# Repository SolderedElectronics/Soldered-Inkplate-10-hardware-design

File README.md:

## --- Product name --- Hardware design

|  |
| :----------------------------------------------------------: |
|      [--- product name ----](https://www.solde.red/SKU)      |

------ product description ------

## Repository contents

All Soldered hardware is designed in KiCAD, and repositories are organized in the following way:

- CAD folder - contains KiCAD files (Schematics, Board, Panel Board), organized by version. Change log lists all changes between versions.
- OUTPUTS - contains useful files, such as Bill of Materials (BOM), PDF of schematics, 3D .step file of the board and gerber files, organized by version. 

## Want to contribute?

All contributions are welcome, feel free to submit the pull request. If you discover a bug, please submit an issue or pull request. 

## About Soldered

At Soldered, we design and manufacture a wide selection of electronic products to help you turn your ideas into acts and bring you one step closer to your final project. Our products are intented for makers and crafted in-house by our experienced team in Osijek, Croatia. We believe that sharing is a crucial element for improvement and innovation, and we work hard to stay connected with all our makers regardless of their skill or experience level. Therefore, all our products are open-source. Finally, we always have your back. If you face any problem concerning either your shopping experience or your electronics project, our team will help you deal with it, offering efficient customer service and cost-free technical support anytime. Some of those might be useful for you:

- [Web Store](https://www.soldered.com)
- [Tutorials & Projects](https://soldered.com/blog)
- [Community & Technical support](https://community.soldered.com)
- [Custom PCBs](https://pcb.soldered.com)

## License info

All Soldered open-source hardware (OSH) is under The TAPR Open Hardware License. Read more in the LICENSE file. 

No warranty - all designs in this repository are distributed in the hope that they will be useful, but without any warranty. They are provided "AS IS", therefore without warranty of any kind, either expressed or implied. The entire quality and performance of what you do with the contents of this repository are your responsibility. In no event, Soldered (TAVU) will be liable for your damages, losses, including any general, special, incidental or consequential damage arising out of the use or inability to use the contents of this repository. 

Thank you from your fellow makers at Soldered.

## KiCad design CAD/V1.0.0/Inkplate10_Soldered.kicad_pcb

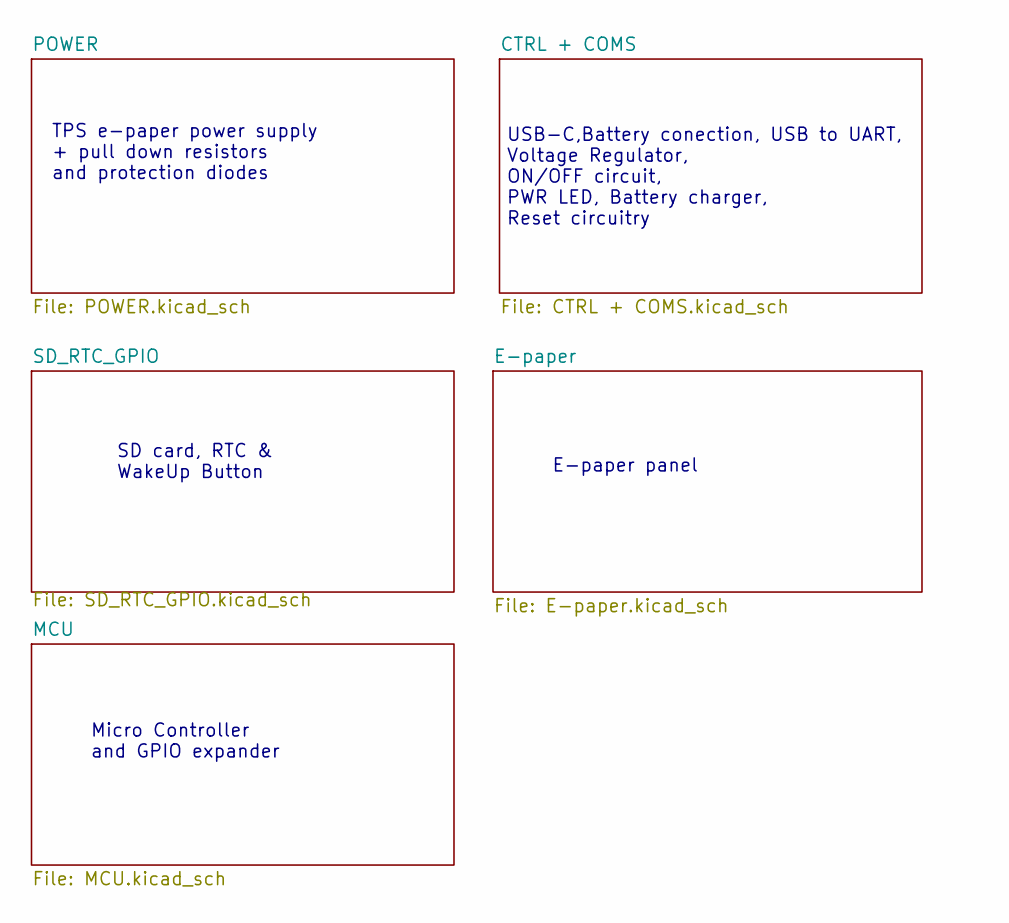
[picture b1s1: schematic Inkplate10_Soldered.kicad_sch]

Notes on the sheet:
SD card, RTC & WakeUp Button
TPS e-paper power supply + pull down resistors and protection diodes
E-paper panel
USB-C,Battery conection, USB to UART, Voltage Regulator, ON/OFF circuit, PWR LED, Battery charger, Reset circuitry
Micro Controller and GPIO expander

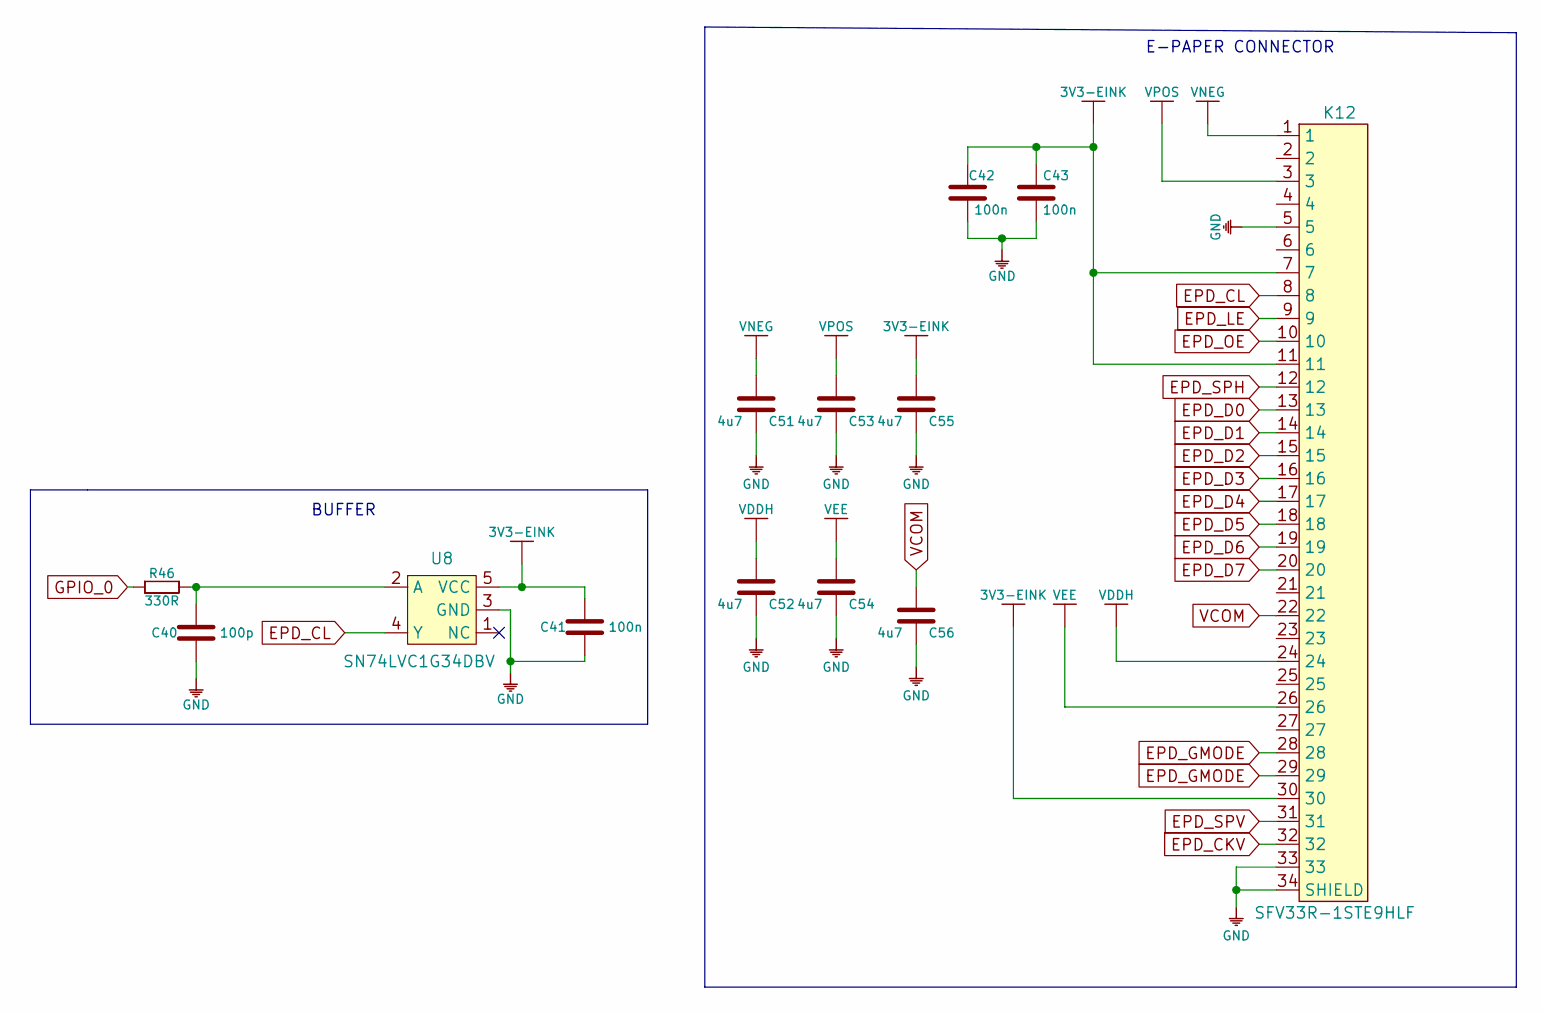
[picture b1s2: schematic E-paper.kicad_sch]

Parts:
C40: 100p; 0603C
C41, C42, C43: 100n; 0603C
C51, C52, C53, C54, C55, C56: 4u7; 0603C
K12: SFV33R-1STE9HLF
R46: 330R; 0603R
U8: SN74LVC1G34DBV

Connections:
3V3-EINK: C41.2, C42.2, C43.2, C55.2, K12.7, K12.11, K12.30, U8.5 (VCC); also elsewhere on the board
EPD_CKV: K12.32; also elsewhere on the board
EPD_CL: K12.8, U8.4 (Y)
EPD_D0: K12.13; also elsewhere on the board
EPD_D1: K12.14; also elsewhere on the board
EPD_D2: K12.15; also elsewhere on the board
EPD_D3: K12.16; also elsewhere on the board
EPD_D4: K12.17; also elsewhere on the board
EPD_D5: K12.18; also elsewhere on the board
EPD_D6: K12.19; also elsewhere on the board
EPD_D7: K12.20; also elsewhere on the board
EPD_GMODE: K12.28, K12.29; also elsewhere on the board
EPD_LE: K12.9; also elsewhere on the board
EPD_OE: K12.10; also elsewhere on the board
EPD_SPH: K12.12; also elsewhere on the board
EPD_SPV: K12.31; also elsewhere on the board
GND: C40.1, C41.1, C42.1, C43.1, C51.1, C52.1, C53.1, C54.1, C55.1, C56.1, K12.5, K12.33, K12.34 (SHIELD), U8.3 (GND); also elsewhere on the board
GPIO_0: R46.1; also elsewhere on the board
unnamed: C40.2, R46.2, U8.2 (A)
VCOM: C56.2, K12.22; also elsewhere on the board
VDDH: C52.2, K12.24; also elsewhere on the board
VEE: C54.2, K12.26; also elsewhere on the board
VNEG: C51.2, K12.1; also elsewhere on the board
VPOS: C53.2, K12.3; also elsewhere on the board

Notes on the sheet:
E-PAPER CONNECTOR
BUFFER

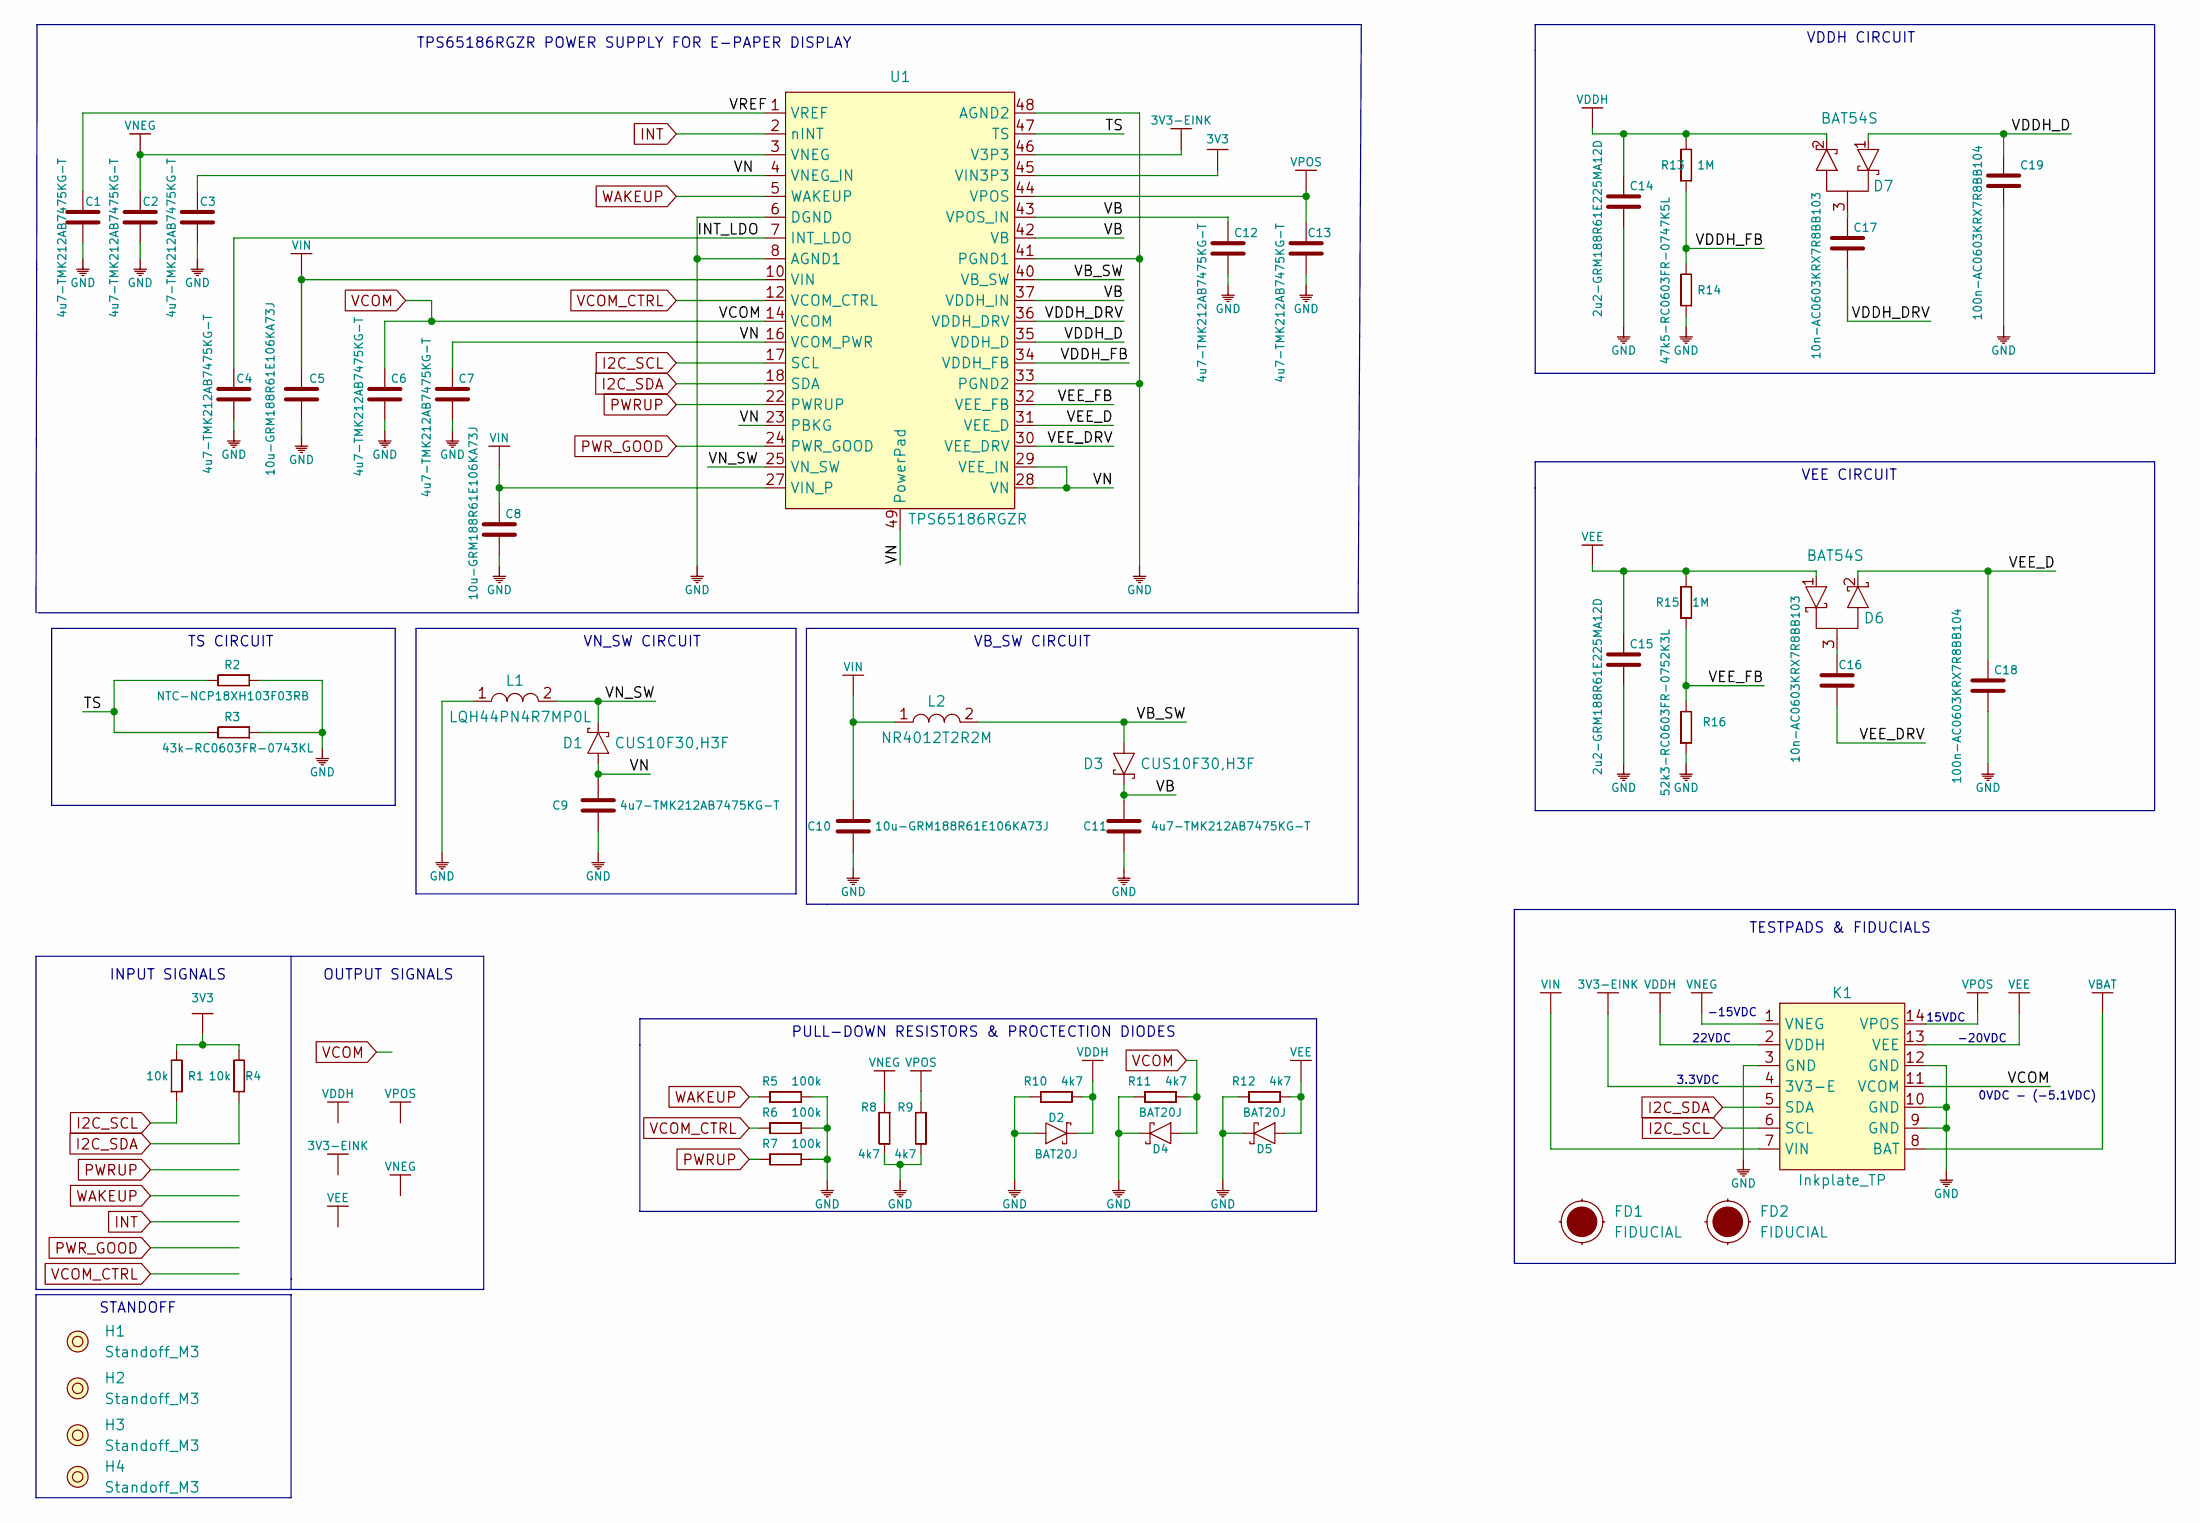
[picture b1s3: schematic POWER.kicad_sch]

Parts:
C1, C2, C3, C4, C6, C7, C9, C11, C12, C13: 4u7-TMK212AB7475KG-T; 0603C
C5, C8, C10: 10u-GRM188R61E106KA73J; 0603C
C14, C15: 2u2-GRM188R61E225MA12D; 0603C
C16, C17: 10n-AC0603KRX7R8BB103; 0603C
C18, C19: 100n-AC0603KRX7R8BB104; 0603C
D1, D3: CUS10F30,H3F; SOD-323-2
D2, D4, D5: BAT20J; SOD-323
D6, D7: BAT54S; SOT-23-3
FD1, FD2: FIDUCIAL; FIDUCIAL_23
H1, H2, H3, H4: Standoff_M3
K1: Inkplate_TP; INKPLATE TEST HEADER
L1: LQH44PN4R7MP0L; 1515L
L2: NR4012T2R2M; NR4012
R1, R4: 10k; 0603R
R2: NTC-NCP18XH103F03RB; 0603R
R3: 43k-RC0603FR-0743KL; 0603R
R5, R6, R7: 100k; 0603R
R8, R9, R10, R11, R12: 4k7; 0603R
R13, R15: 1M; 0603R
R14: 47k5-RC0603FR-0747K5L; 0603R
R16: 52k3-RC0603FR-0752K3L; 0603R
U1: TPS65186RGZR; VQFN-49

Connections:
3V3: R1.2, R4.2, U1.45 (VIN3P3); also elsewhere on the board
3V3-EINK: K1.4 (3V3-E), U1.46 (V3P3); also elsewhere on the board
/POWER/INT_LDO: C4.2, U1.7 (INT_LDO)
/POWER/TS: R2.2, R3.2, U1.47 (TS)
/POWER/VB: C11.2, C12.1, D3.1 (C), U1.37 (VDDH_IN), U1.42 (VB), U1.43 (VPOS_IN)
/POWER/VB_SW: D3.2 (A), L2.2, U1.40 (VB_SW)
/POWER/VDDH_D: C19.2, D7.1 (A), U1.35 (VDDH_D)
/POWER/VDDH_DRV: C17.1, U1.36 (VDDH_DRV)
/POWER/VDDH_FB: R13.1, R14.2, U1.34 (VDDH_FB)
/POWER/VEE_D: C18.2, D6.2 (K), U1.31 (VEE_D)
/POWER/VEE_DRV: C16.2, U1.30 (VEE_DRV)
/POWER/VEE_FB: R15.1, R16.2, U1.32 (VEE_FB)
/POWER/VN: C3.2, C7.1, C9.2, D1.2 (A), U1.4 (VNEG_IN), U1.16 (VCOM_PWR), U1.23 (PBKG), U1.28 (VN), U1.29 (VEE_IN), U1.49 (PowerPad)
/POWER/VN_SW: D1.1 (C), L1.2, U1.25 (VN_SW)
/POWER/VREF: C1.2, U1.1 (VREF)
GND: C1.1, C2.1, C3.1, C4.1, C5.1, C6.2, C7.2, C8.1, C9.1, C10.1, C11.1, C12.2, C13.2, C14.1, C15.1, C18.1, C19.1, D2.1 (A), D4.2 (C), D5.2 (C), K1.3 (GND), K1.9 (GND), K1.10 (GND), K1.12 (GND), L1.1, R2.1, R3.1, R5.2, R6.2, R7.2, R8.2, R9.2, R10.1, R11.1, R12.1, R14.1, R16.1, U1.6 (DGND), U1.8 (AGND1), U1.33 (PGND2), U1.41 (PGND1), U1.48 (AGND2); also elsewhere on the board
I2C_SCL: K1.6 (SCL), R1.1, U1.17 (SCL); also elsewhere on the board
I2C_SDA: K1.5 (SDA), R4.1, U1.18 (SDA); also elsewhere on the board
INT: U1.2 (nINT); also elsewhere on the board
unnamed: C16.1, D6.3
unnamed: C17.2, D7.3
PWRUP: R7.1, U1.22 (PWRUP); also elsewhere on the board
PWR_GOOD: U1.24 (PWR_GOOD); also elsewhere on the board
VBAT: K1.8 (BAT); also elsewhere on the board
VCOM: C6.1, D4.1 (A), K1.11 (VCOM), R11.2, U1.14 (VCOM); also elsewhere on the board
VCOM_CTRL: R6.1, U1.12 (VCOM_CTRL); also elsewhere on the board
VDDH: C14.2, D2.2 (C), D7.2 (K), K1.2 (VDDH), R10.2, R13.2; also elsewhere on the board
VEE: C15.2, D5.1 (A), D6.1 (A), K1.13 (VEE), R12.2, R15.2; also elsewhere on the board
VIN: C5.2, C8.2, C10.2, K1.7 (VIN), L2.1, U1.10 (VIN), U1.27 (VIN_P); also elsewhere on the board
VNEG: C2.2, K1.1 (VNEG), R8.1, U1.3 (VNEG); also elsewhere on the board
VPOS: C13.1, K1.14 (VPOS), R9.1, U1.44 (VPOS); also elsewhere on the board
WAKEUP: R5.1, U1.5 (WAKEUP); also elsewhere on the board

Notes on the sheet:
TPS65186RGZR POWER SUPPLY FOR E-PAPER DISPLAY
VB_SW CIRCUIT
VDDH CIRCUIT
VEE CIRCUIT
INPUT SIGNALS
OUTPUT SIGNALS
TS CIRCUIT
PULL-DOWN RESISTORS & PROCTECTION DIODES
TESTPADS & FIDUCIALS
VN_SW CIRCUIT
3.3VDC
-20VDC
22VDC
STANDOFF
0VDC - (-5.1VDC)
-15VDC
15VDC

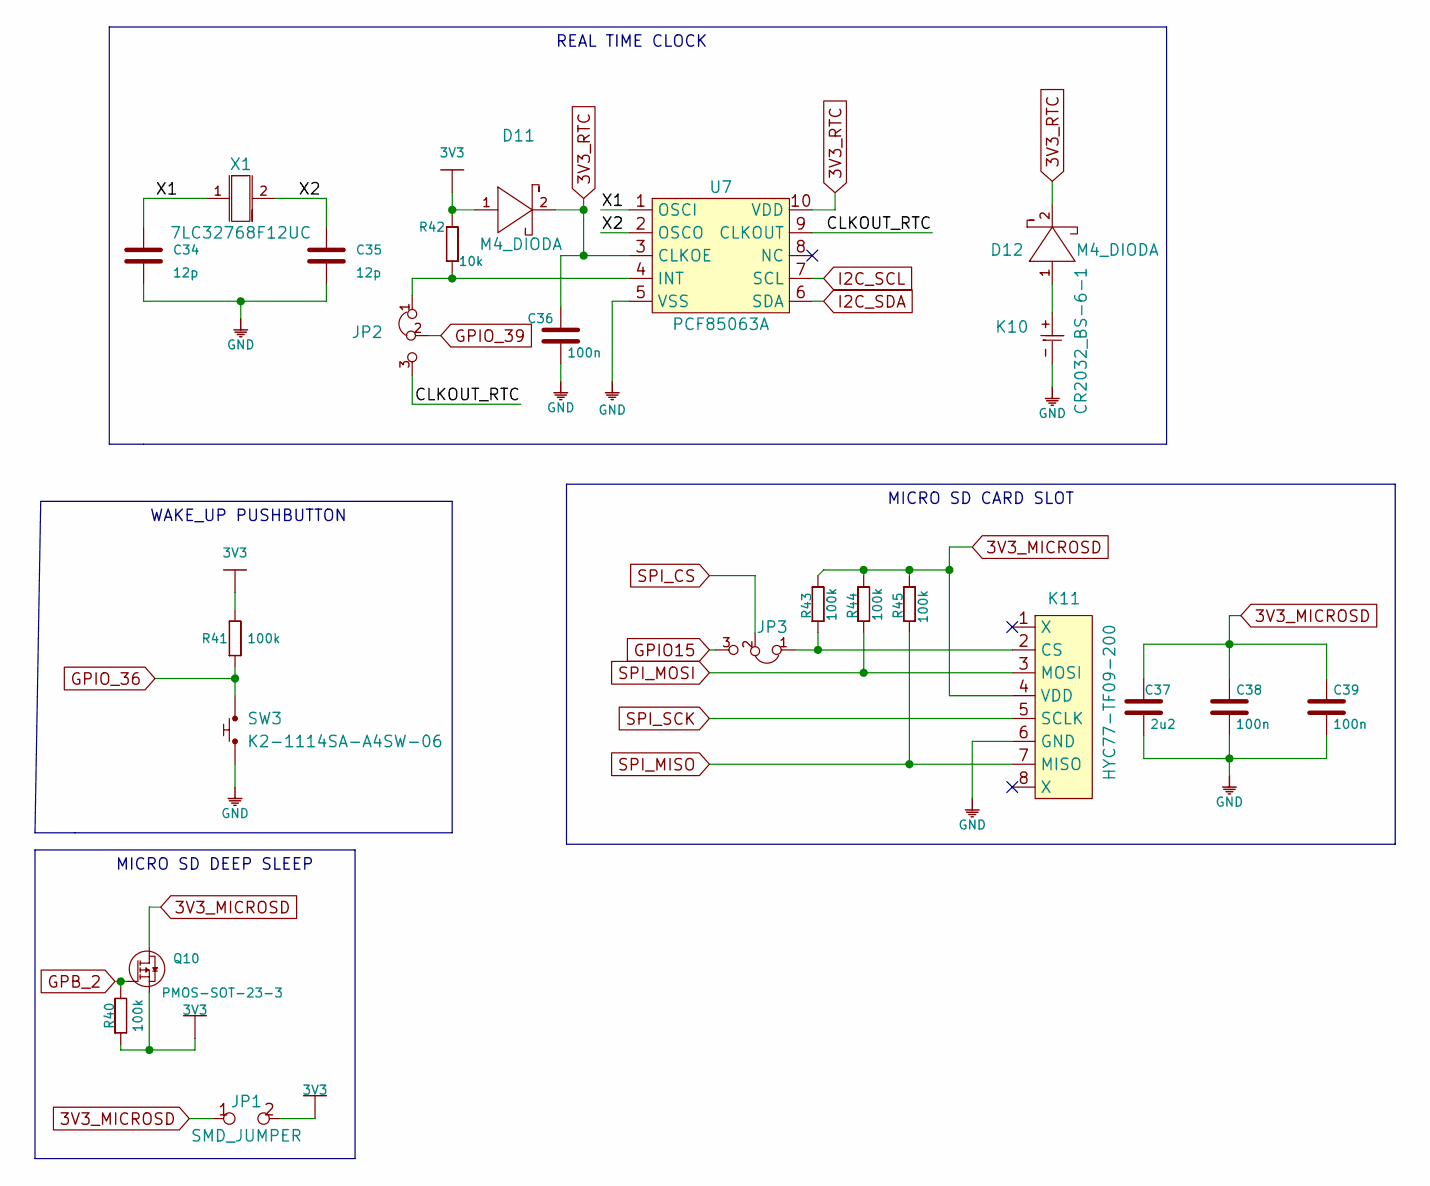
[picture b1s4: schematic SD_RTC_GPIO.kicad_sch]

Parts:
C34, C35: 12p; 0603C
C36, C38, C39: 100n; 0603C
C37: 2u2; 0603C
D11, D12: M4_DIODA
JP1: SMD_JUMPER
JP2, JP3: SMD_JUMPER_3_PAD_CONNECTED_LEFT_TRACE
K10: CR2032_BS-6-1; CR2032-BS-6-1
K11: HYC77-TF09-200
Q10: PMOS-SOT-23-3; SOT-23-3
R40, R41, R43, R44, R45: 100k; 0603R
R42: 10k; 0603R
SW3: K2-1114SA-A4SW-06
U7: PCF85063A
X1: 7LC32768F12UC; ABS07AIG-32.768KHZ-7-D-T

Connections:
3V3: D11.1 (A), JP1.2, Q10.2 (S), R40.1, R41.2, R42.2; also elsewhere on the board
3V3_MICROSD: C37.2, C38.2, C39.2, JP1.1, K11.4 (VDD), Q10.3 (D), R43.2, R44.2, R45.2
3V3_RTC: C36.2, D11.2 (K), D12.2 (K), U7.3 (CLKOE), U7.10 (VDD)
/SD_RTC_GPIO/CLKOUT_RTC: JP2.3, U7.9 (CLKOUT)
/SD_RTC_GPIO/X1: C34.2, U7.1 (OSCI), X1.1
/SD_RTC_GPIO/X2: C35.2, U7.2 (OSCO), X1.2
GND: C34.1, C35.1, C36.1, C37.1, C38.1, C39.1, K10.-, K11.6 (GND), SW3.1, U7.5 (VSS); also elsewhere on the board
GPB_2: Q10.1 (G), R40.2; also elsewhere on the board
GPIO15: JP3.3; also elsewhere on the board
GPIO_36: R41.1, SW3.2; also elsewhere on the board
GPIO_39: JP2.2; also elsewhere on the board
I2C_SCL: U7.7 (SCL); also elsewhere on the board
I2C_SDA: U7.6 (SDA); also elsewhere on the board
unnamed: D12.1 (A), K10.+
unnamed: JP2.1, R42.1, U7.4 (INT)
unnamed: JP3.1, K11.2 (CS), R43.1
SPI_CS: JP3.2; also elsewhere on the board
SPI_MISO: K11.7 (MISO), R45.1; also elsewhere on the board
SPI_MOSI: K11.3 (MOSI), R44.1; also elsewhere on the board
SPI_SCK: K11.5 (SCLK); also elsewhere on the board

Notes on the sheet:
WAKE_UP PUSHBUTTON
MICRO SD DEEP SLEEP
MICRO SD CARD SLOT
REAL TIME CLOCK

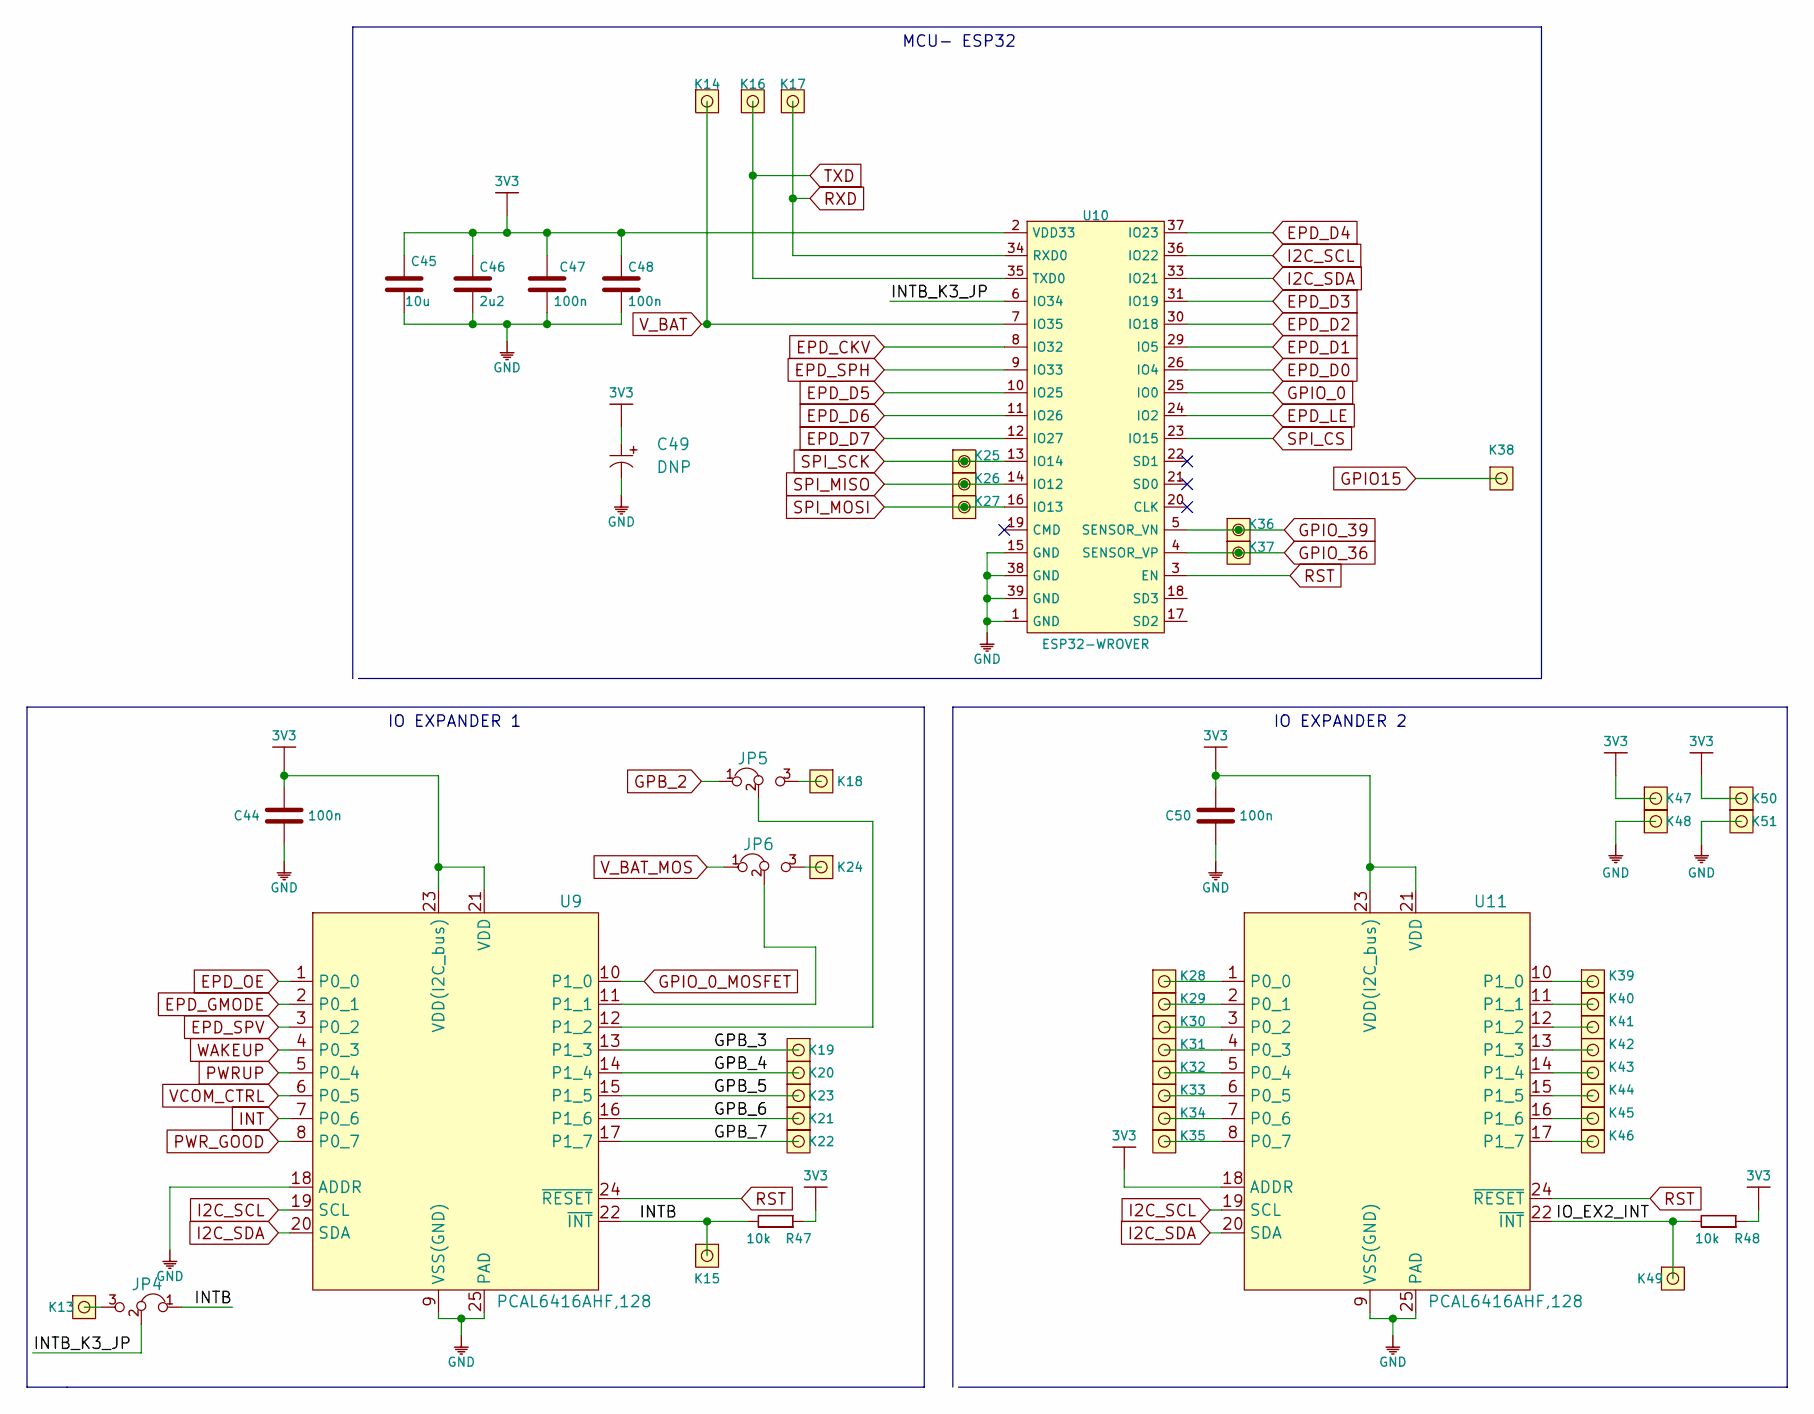
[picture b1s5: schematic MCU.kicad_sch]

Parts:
C44, C47, C48, C50: 100n; 0603C
C45: 10u; 1206C
C46: 2u2; 0603C
C49: DNP; 2917C
JP4, JP5, JP6: SMD_JUMPER_3_PAD_CONNECTED_LEFT_TRACE
K13, K14, K15, K16, K17, K18, K19, K20, K21, K22, K23, K24, K25, K26, K27, K28, K29, K30, K31, K32, K33, K34, K35, K36, K37, K38, K39, K40, K41, K42, K43, K44, K45, K46, K47, K48, K49, K50, K51: HEADER_MALE_1X1_Inkplate
R47, R48: 10k; 0603R
U9, U11: PCAL6416AHF,128
U10: ESP32-WROVER

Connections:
3V3: C44.2, C45.2, C46.2, C47.2, C48.2, C49.1 (+), C50.2, K47.1, K50.1, R47.1, R48.1, U9.21 (VDD), U9.23 (VDD(I2C_bus)), U10.2 (VDD33), U11.18 (ADDR), U11.21 (VDD), U11.23 (VDD(I2C_bus)); also elsewhere on the board
/MCU/GPB_3: K19.1, U9.13 (P1_3)
/MCU/GPB_4: K20.1, U9.14 (P1_4)
/MCU/GPB_5: K23.1, U9.15 (P1_5)
/MCU/GPB_6: K21.1, U9.16 (P1_6)
/MCU/GPB_7: K22.1, U9.17 (P1_7)
/MCU/INTB: JP4.1, K15.1, R47.2, U9.22 (~INT)
/MCU/INTB_K3_JP: JP4.2, U10.6 (IO34)
/MCU/IO_EX2_INT: K49.1, R48.2, U11.22 (~INT)
EPD_CKV: U10.8 (IO32); also elsewhere on the board
EPD_D0: U10.26 (IO4); also elsewhere on the board
EPD_D1: U10.29 (IO5); also elsewhere on the board
EPD_D2: U10.30 (IO18); also elsewhere on the board
EPD_D3: U10.31 (IO19); also elsewhere on the board
EPD_D4: U10.37 (IO23); also elsewhere on the board
EPD_D5: U10.10 (IO25); also elsewhere on the board
EPD_D6: U10.11 (IO26); also elsewhere on the board
EPD_D7: U10.12 (IO27); also elsewhere on the board
EPD_GMODE: U9.2 (P0_1); also elsewhere on the board
EPD_LE: U10.24 (IO2); also elsewhere on the board
EPD_OE: U9.1 (P0_0); also elsewhere on the board
EPD_SPH: U10.9 (IO33); also elsewhere on the board
EPD_SPV: U9.3 (P0_2); also elsewhere on the board
GND: C44.1, C45.1, C46.1, C47.1, C48.1, C49.2 (-), C50.1, K48.1, K51.1, U9.9 (VSS(GND)), U9.18 (ADDR), U9.25 (PAD), U10.1 (GND), U10.15 (GND), U10.38 (GND), U10.39 (GND), U11.9 (VSS(GND)), U11.25 (PAD); also elsewhere on the board
GPB_2: JP5.1; also elsewhere on the board
GPIO15: K38.1; also elsewhere on the board
GPIO_0: U10.25 (IO0); also elsewhere on the board
GPIO_0_MOSFET: U9.10 (P1_0); also elsewhere on the board
GPIO_36: K37.1, U10.4 (SENSOR_VP); also elsewhere on the board
GPIO_39: K36.1, U10.5 (SENSOR_VN); also elsewhere on the board
I2C_SCL: U9.19 (SCL), U10.36 (IO22), U11.19 (SCL); also elsewhere on the board
I2C_SDA: U9.20 (SDA), U10.33 (IO21), U11.20 (SDA); also elsewhere on the board
INT: U9.7 (P0_6); also elsewhere on the board
unnamed: JP4.3, K13.1
unnamed: JP5.3, K18.1
unnamed: JP6.2, U9.11 (P1_1)
unnamed: JP6.3, K24.1
unnamed: K28.1, U11.1 (P0_0)
unnamed: K29.1, U11.2 (P0_1)
unnamed: K30.1, U11.3 (P0_2)
unnamed: K31.1, U11.4 (P0_3)
unnamed: K32.1, U11.5 (P0_4)
unnamed: K33.1, U11.6 (P0_5)
unnamed: K34.1, U11.7 (P0_6)
unnamed: K35.1, U11.8 (P0_7)
unnamed: K39.1, U11.10 (P1_0)
unnamed: K40.1, U11.11 (P1_1)
unnamed: K41.1, U11.12 (P1_2)
unnamed: K42.1, U11.13 (P1_3)
unnamed: K43.1, U11.14 (P1_4)
unnamed: K44.1, U11.15 (P1_5)
unnamed: K45.1, U11.16 (P1_6)
unnamed: K46.1, U11.17 (P1_7)
unnamed: JP5.2, U9.12 (P1_2)
PWRUP: U9.5 (P0_4); also elsewhere on the board
PWR_GOOD: U9.8 (P0_7); also elsewhere on the board
RST: U9.24 (~RESET), U10.3 (EN), U11.24 (~RESET); also elsewhere on the board
RXD: K17.1, U10.34 (RXD0); also elsewhere on the board
SPI_CS: U10.23 (IO15); also elsewhere on the board
SPI_MISO: K26.1, U10.14 (IO12); also elsewhere on the board
SPI_MOSI: K27.1, U10.16 (IO13); also elsewhere on the board
SPI_SCK: K25.1, U10.13 (IO14); also elsewhere on the board
TXD: K16.1, U10.35 (TXD0); also elsewhere on the board
VCOM_CTRL: U9.6 (P0_5); also elsewhere on the board
V_BAT: K14.1, U10.7 (IO35); also elsewhere on the board
V_BAT_MOS: JP6.1; also elsewhere on the board
WAKEUP: U9.4 (P0_3); also elsewhere on the board

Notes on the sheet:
IO EXPANDER 1
IO EXPANDER 2
MCU- ESP32

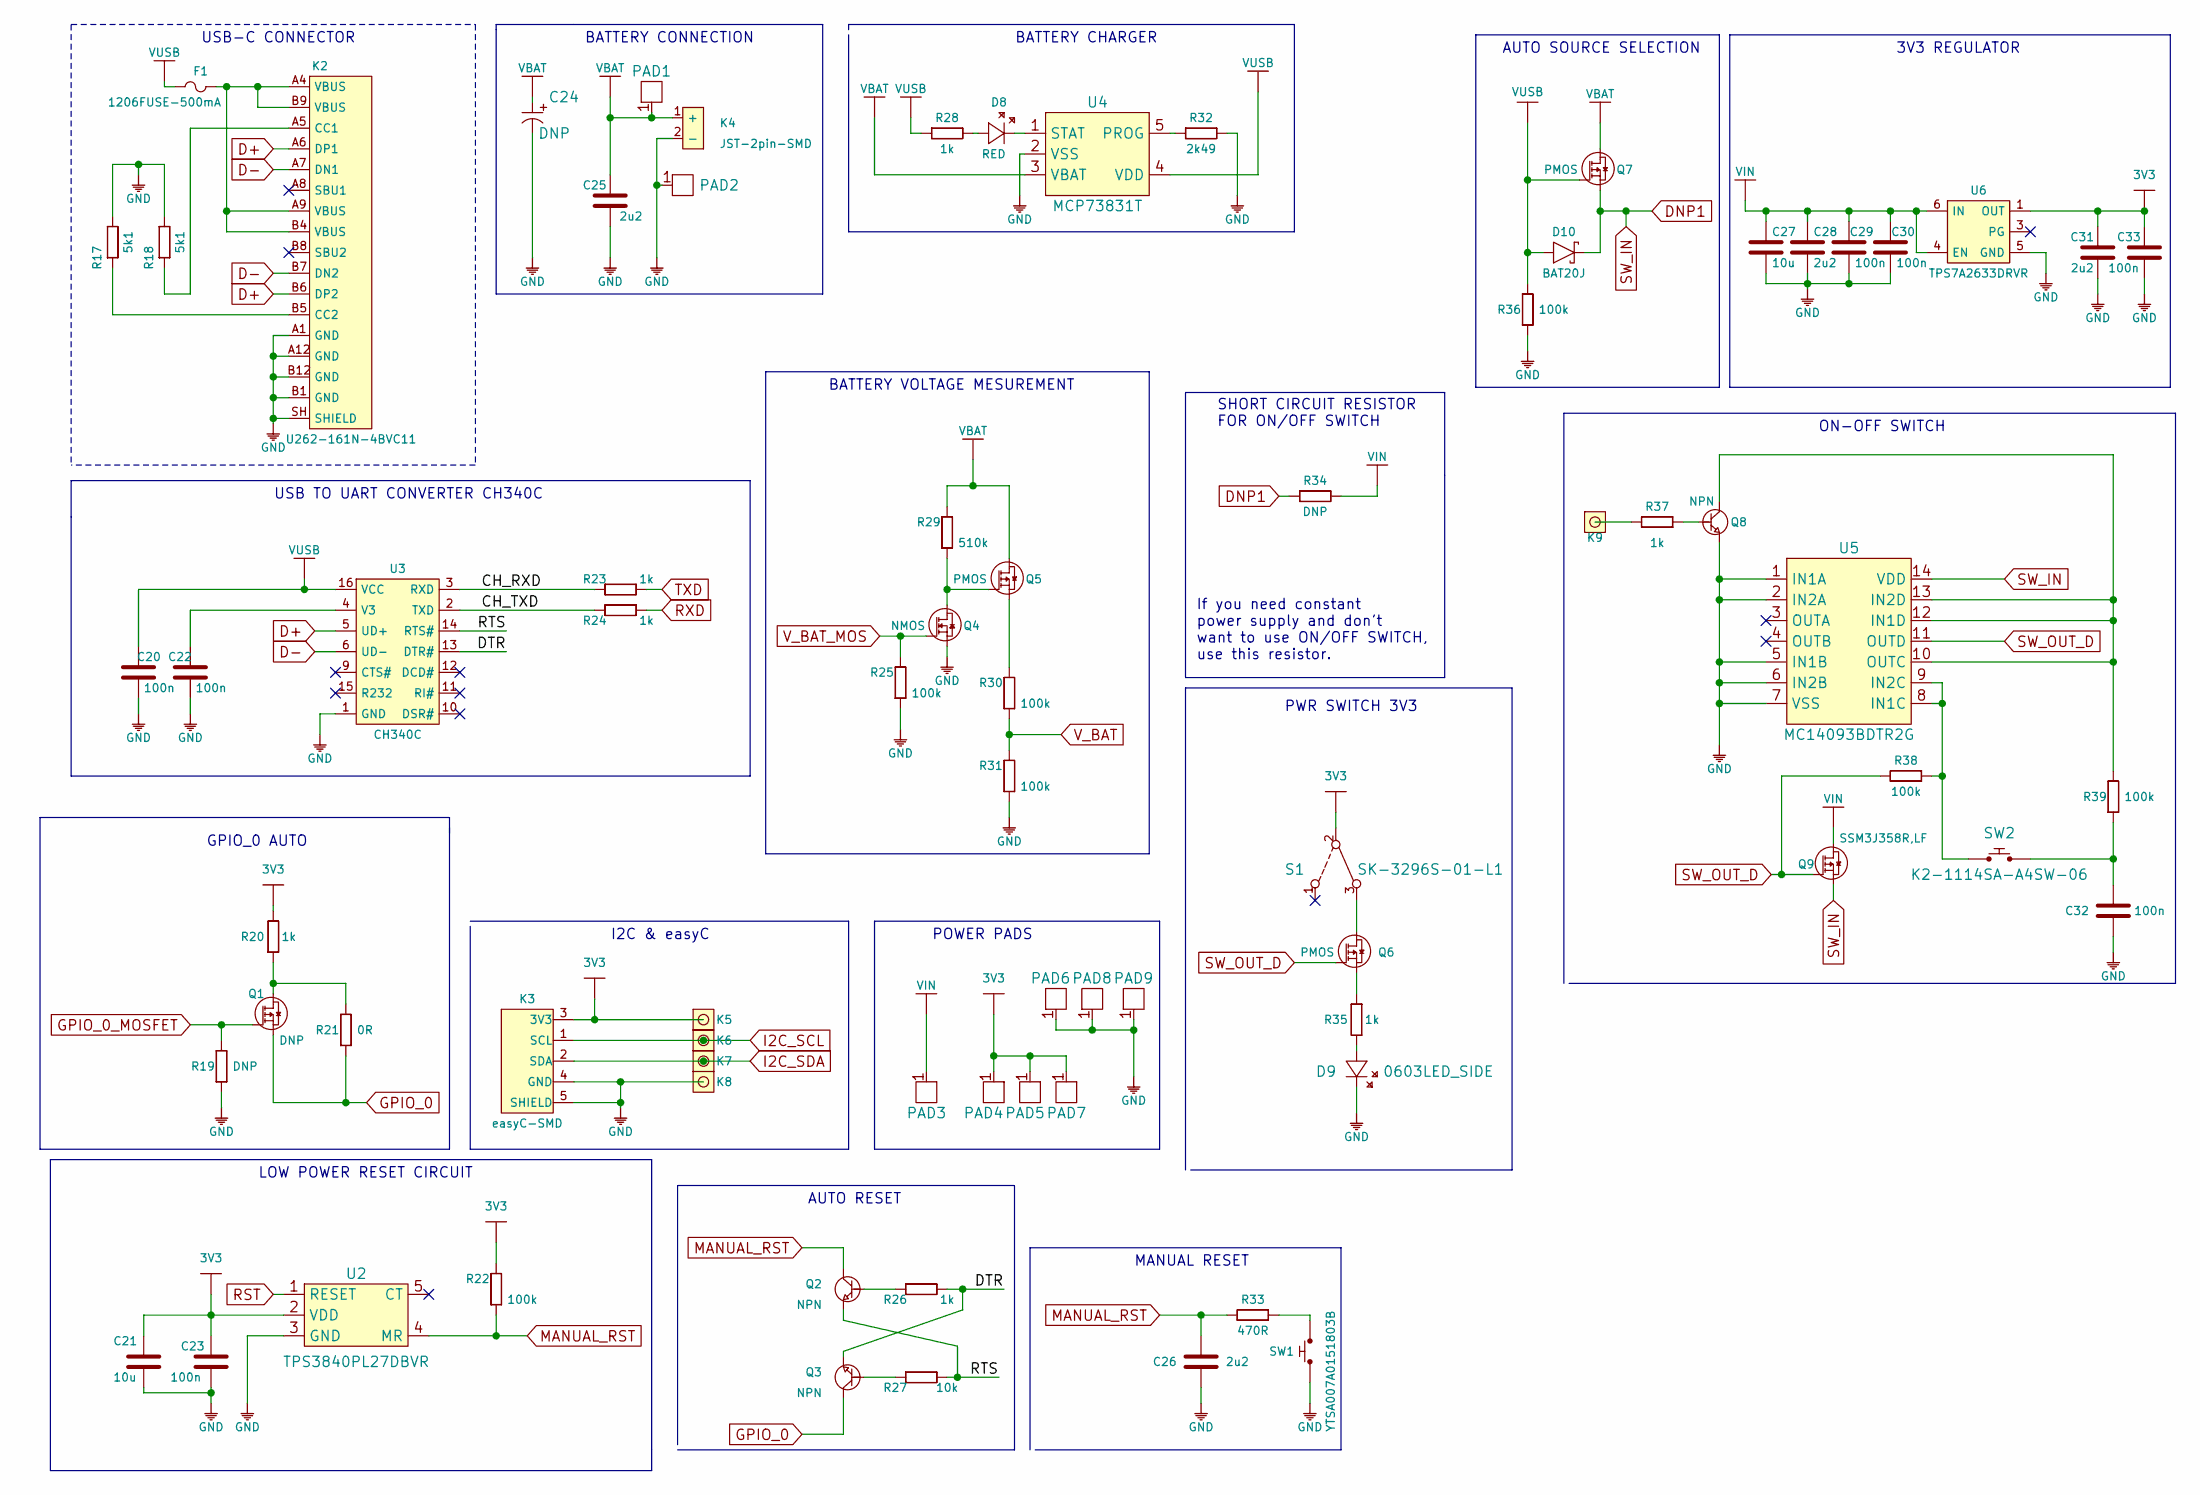
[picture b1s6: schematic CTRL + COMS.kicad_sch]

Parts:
C20, C22, C23, C29, C30, C32, C33: 100n; 0603C
C21, C27: 10u; 1206C
C24: DNP; 2917C
C25, C26, C28, C31: 2u2; 0603C
D8: RED; 0402LED
D9: 0603LED_SIDE; LTST-S270GKT
D10: BAT20J; SOD-323
F1: 1206FUSE-500mA; 1206FUSE
K2: U262-161N-4BVC11
K3: easyC-SMD; easyC-connector
K4: JST-2pin-SMD
K5, K6, K7, K8, K9: HEADER_MALE_1X1_Inkplate
PAD1, PAD2, PAD3, PAD4, PAD5, PAD6, PAD7, PAD8, PAD9: PAD_4x4
Q1: DNP; SOT-23-3
Q2, Q3, Q8: NPN; SOT-23-3
Q4: NMOS; SOT-23-3
Q5, Q6, Q7: PMOS; SOT-23-3
Q9: SSM3J358R,LF; SOT-23-3
R17, R18: 5k1; 0603R
R19, R34: DNP; 0603R
R20, R23, R24, R26, R28, R35, R37: 1k; 0603R
R21: 0R; 0603R
R22, R25, R30, R31, R36, R38, R39: 100k; 0603R
R27: 10k; 0603R
R29: 510k; 0603R
R32: 2k49; 0603R
R33: 470R; 0603R
S1: SK-3296S-01-L1
SW1: YTSA007A0151803B
SW2: K2-1114SA-A4SW-06
U2: TPS3840PL27DBVR; SOT-23-5
U3: CH340C; SOP-16
U4: MCP73831T; SOT-23-5
U5: MC14093BDTR2G; TSSOP-14
U6: TPS7A2633DRVR

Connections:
3V3: C21.2, C23.2, C31.2, C33.2, K3.3 (3V3), K5.1, PAD4.1, PAD5.1, PAD7.1, R20.2, R22.2, S1.2, U2.2 (VDD), U6.1 (OUT); also elsewhere on the board
/CTRL + COMS/CH_RXD: R23.1, U3.3 (RXD)
/CTRL + COMS/CH_TXD: R24.1, U3.2 (TXD)
/CTRL + COMS/DTR: Q3.2 (E), R26.2, U3.13 (DTR#)
/CTRL + COMS/RTS: Q2.2 (E), R27.2, U3.14 (RTS#)
D+: K2.A6 (DP1), K2.B6 (DP2), U3.5 (UD+)
D-: K2.A7 (DN1), K2.B7 (DN2), U3.6 (UD-)
DNP1: D10.2 (C), Q7.2 (S), Q9.2 (S), R34.1, U5.14 (VDD)
GND: C20.1, C21.1, C22.1, C23.1, C24.2 (-), C25.1, C26.1, C27.1, C28.1, C29.1, C30.1, C31.1, C32.1, C33.1, D9.2 (K), K2.A1 (GND), K2.A12 (GND), K2.B1 (GND), K2.B12 (GND), K2.SH (SHIELD), K3.4 (GND), K3.5 (SHIELD), K4.2 (-), K8.1, PAD2.1, PAD6.1, PAD8.1, PAD9.1, Q4.2 (S), Q8.2 (E), R17.2, R18.2, R19.1, R25.1, R31.1, R32.2, R36.1, SW1.1, U2.3 (GND), U3.1 (GND), U4.2 (VSS), U5.1 (IN1A), U5.2 (IN2A), U5.5 (IN1B), U5.6 (IN2B), U5.7 (VSS), U6.5 (GND); also elsewhere on the board
GPIO_0: Q1.2 (S), Q3.3 (C), R21.1; also elsewhere on the board
GPIO_0_MOSFET: Q1.1 (G), R19.2; also elsewhere on the board
I2C_SCL: K3.1 (SCL), K6.1; also elsewhere on the board
I2C_SDA: K3.2 (SDA), K7.1; also elsewhere on the board
MANUAL_RST: C26.2, Q2.3 (C), R22.1, R33.2, U2.4 (MR)
unnamed: C22.2, U3.4 (V3)
unnamed: C32.2, R39.1, SW2.2
unnamed: D8.1 (A), R28.2
unnamed: D8.2 (K), U4.1 (STAT)
unnamed: D9.1 (A), R35.2
unnamed: F1.2, K2.A4 (VBUS), K2.A9 (VBUS), K2.B4 (VBUS), K2.B9 (VBUS)
unnamed: K2.A5 (CC1), R18.1
unnamed: K2.B5 (CC2), R17.1
unnamed: K9.1, R37.2
unnamed: Q1.3 (D), R20.1, R21.2
unnamed: Q2.1 (B), R26.1
unnamed: Q3.1 (B), R27.1
unnamed: Q4.3 (D), Q5.1 (G), R29.1
unnamed: Q5.2 (S), R30.2
unnamed: Q6.2 (S), R35.1
unnamed: Q6.3 (D), S1.3
unnamed: Q8.1 (B), R37.1
unnamed: Q8.3 (C), R39.2, U5.10 (OUTC), U5.12 (IN1D), U5.13 (IN2D)
unnamed: R32.1, U4.5 (PROG)
unnamed: R33.1, SW1.2
unnamed: R38.1, SW2.1, U5.8 (IN1C), U5.9 (IN2C)
RST: U2.1 (RESET); also elsewhere on the board
RXD: R24.2; also elsewhere on the board
SW_OUT_D: Q6.1 (G), Q9.1 (G), R38.2, U5.11 (OUTD)
TXD: R23.2; also elsewhere on the board
VBAT: C24.1 (+), C25.2, K4.1 (+), PAD1.1, Q5.3 (D), Q7.3 (D), R29.2, U4.3 (VBAT); also elsewhere on the board
VIN: C27.2, C28.2, C29.2, C30.2, PAD3.1, Q9.3 (D), R34.2, U6.4 (EN), U6.6 (IN); also elsewhere on the board
VUSB: C20.2, D10.1 (A), F1.1, Q7.1 (G), R28.1, R36.2, U3.16 (VCC), U4.4 (VDD)
V_BAT: R30.1, R31.2; also elsewhere on the board
V_BAT_MOS: Q4.1 (G), R25.2; also elsewhere on the board

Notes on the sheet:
If you need constant power supply and don't want to use ON/OFF SWITCH, use this resistor.
AUTO SOURCE SELECTION
USB-C CONNECTOR
ON-OFF SWITCH
PWR SWITCH 3V3
POWER PADS
3V3 REGULATOR
BATTERY VOLTAGE MESUREMENT
BATTERY CONNECTION
AUTO RESET
MANUAL RESET
GPIO_0 AUTO
SHORT CIRCUIT RESISTOR FOR ON/OFF SWITCH
BATTERY CHARGER
LOW POWER RESET CIRCUIT
USB TO UART CONVERTER CH340C
I2C & easyC
